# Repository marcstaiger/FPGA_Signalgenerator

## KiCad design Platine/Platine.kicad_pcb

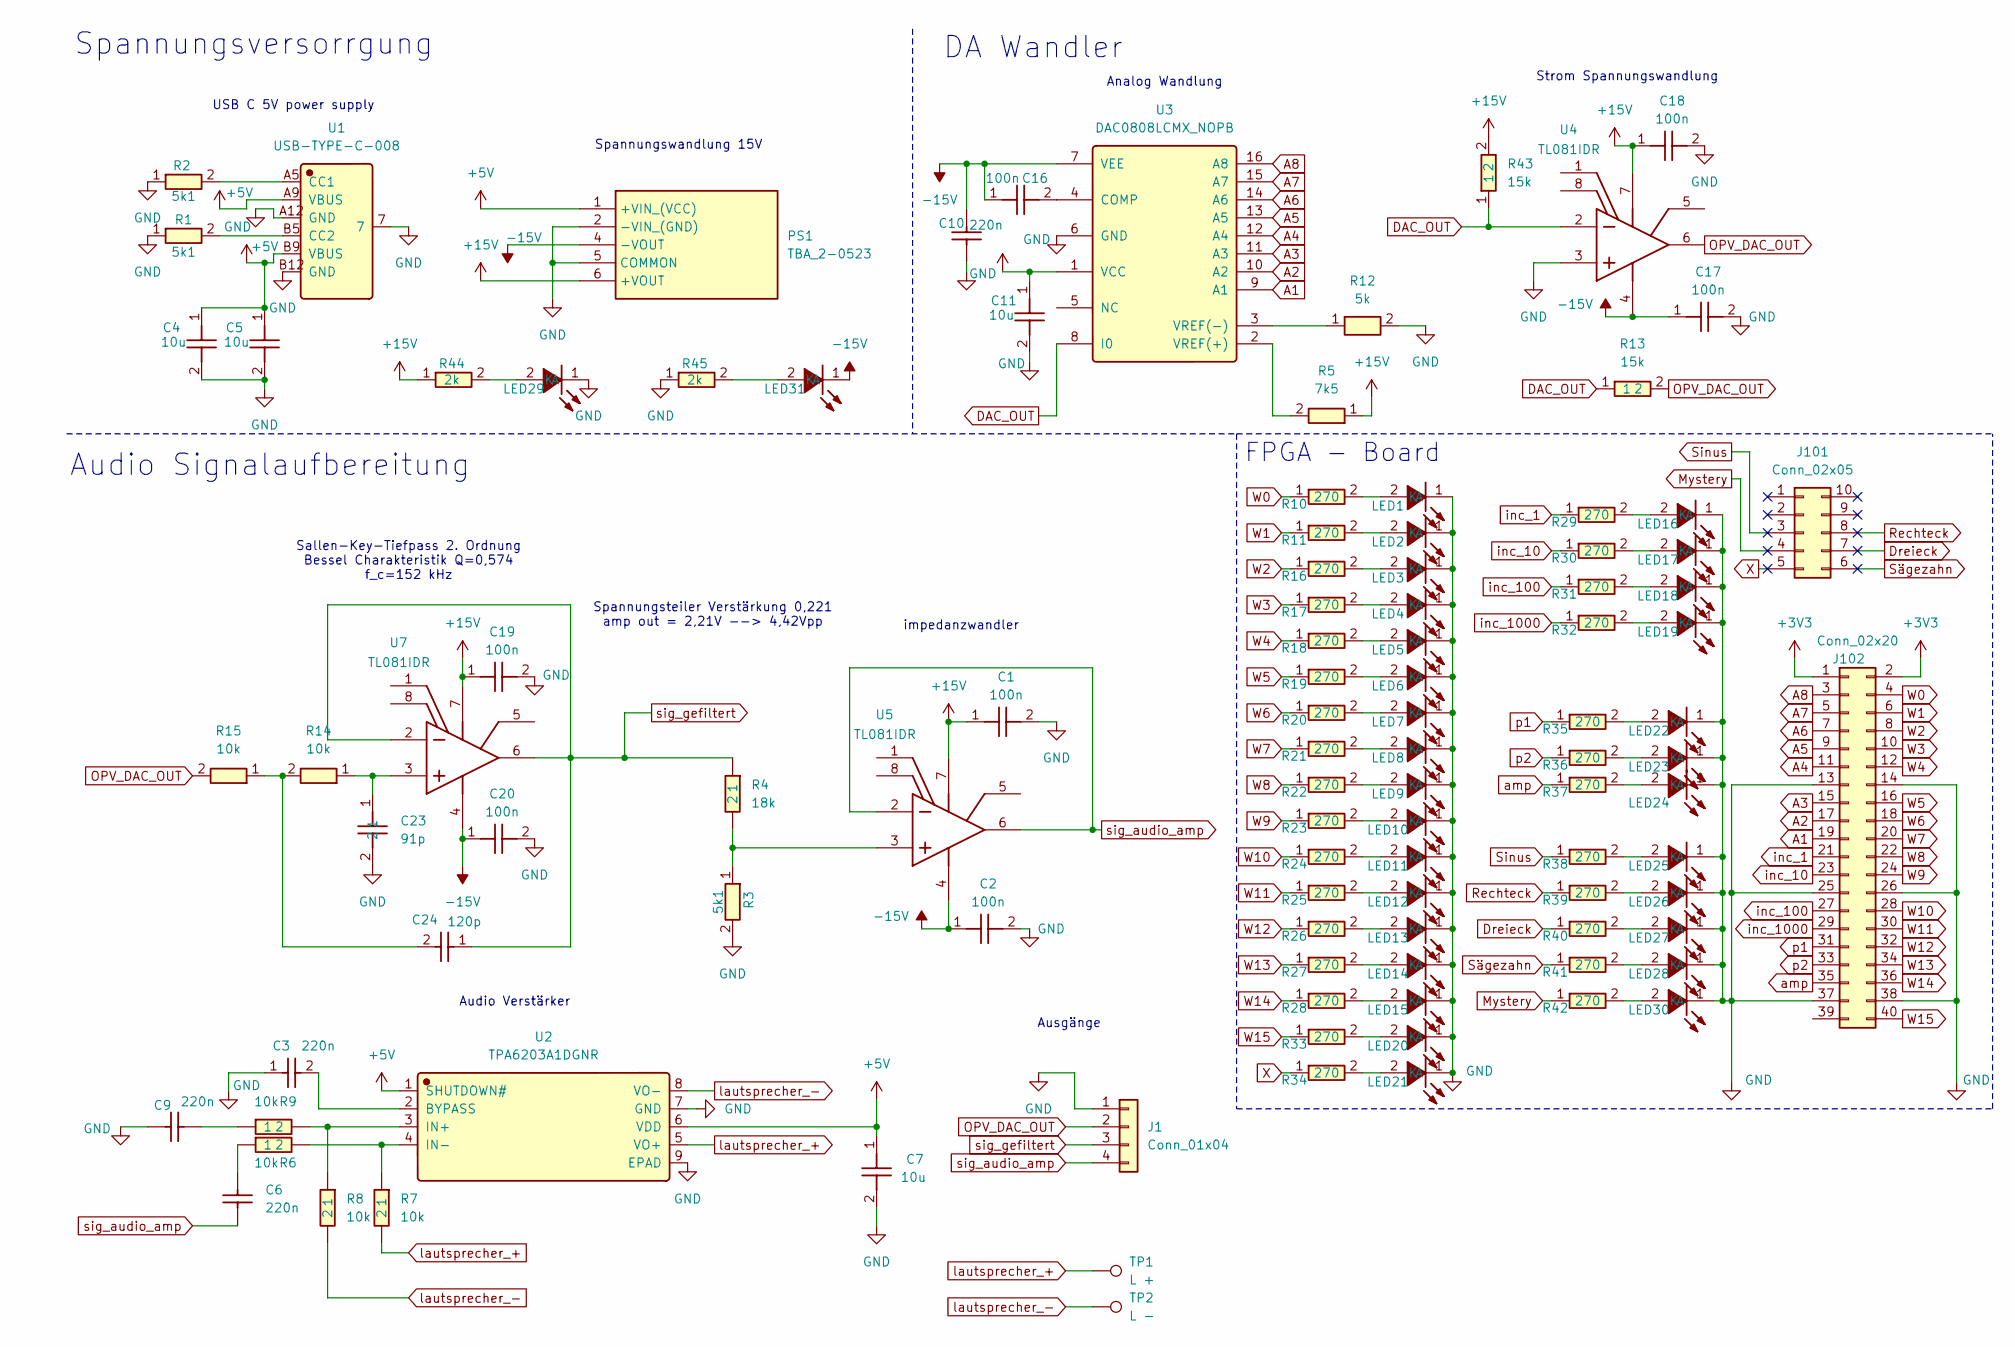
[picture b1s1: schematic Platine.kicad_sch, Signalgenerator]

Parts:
C1, C2, C16, C17, C18, C19, C20: 100n; CL05B104KO5NNNC; Manufacturer Part CL05B104KO5NNNC; LCSC C1525
C3, C6, C9, C10: 220n; CL21B224KBFNNNE; Manufacturer Part CL21B224KBFNNNE; LCSC C5378
C4, C5, C7, C11: 10u; CL21A106KAYNNNE; Manufacturer Part CL21A106KAYNNNE; LCSC C15850
C23: 91p; CC0402FRNPO9BN910; Manufacturer Part CC0402FRNPO9BN910; LCSC C541440
C24: 120p; GCM1555C1H121FA16D; Manufacturer Part GCM1555C1H121FA16D; LCSC C126496
J1: Conn_01x04; PinHeader_1x04_P2.54mm_Vertical
J101: Conn_02x05; PinHeader_2x05_P2.54mm_Vertical
J102: Conn_02x20; PinHeader_2x20_P2.54mm_Vertical
LED1: W0; KT-0603R; Manufacturer Part KT-0603R; LCSC C2286
LED2: W1; KT-0603R; Manufacturer Part KT-0603R; LCSC C2286
LED3: W2; KT-0603R; Manufacturer Part KT-0603R; LCSC C2286
LED4: W3; KT-0603R; Manufacturer Part KT-0603R; LCSC C2286
LED5: W4; KT-0603R; Manufacturer Part KT-0603R; LCSC C2286
LED6: W5; KT-0603R; Manufacturer Part KT-0603R; LCSC C2286
LED7: W6; KT-0603R; Manufacturer Part KT-0603R; LCSC C2286
LED8: W7; KT-0603R; Manufacturer Part KT-0603R; LCSC C2286
LED9: W8; KT-0603R; Manufacturer Part KT-0603R; LCSC C2286
LED10: W9; KT-0603R; Manufacturer Part KT-0603R; LCSC C2286
LED11: W10; KT-0603R; Manufacturer Part KT-0603R; LCSC C2286
LED12: W11; KT-0603R; Manufacturer Part KT-0603R; LCSC C2286
LED13: W12; KT-0603R; Manufacturer Part KT-0603R; LCSC C2286
LED14: W13; KT-0603R; Manufacturer Part KT-0603R; LCSC C2286
LED15: W14; KT-0603R; Manufacturer Part KT-0603R; LCSC C2286
LED16: inc_1; KT-0603R; Manufacturer Part KT-0603R; LCSC C2286
LED17: inc_10; KT-0603R; Manufacturer Part KT-0603R; LCSC C2286
LED18: inc_100; KT-0603R; Manufacturer Part KT-0603R; LCSC C2286
LED19: inc_1000; KT-0603R; Manufacturer Part KT-0603R; LCSC C2286
LED20: W15; KT-0603R; Manufacturer Part KT-0603R; LCSC C2286
LED21: X; KT-0603R; Manufacturer Part KT-0603R; LCSC C2286
LED22: p1; KT-0603R; Manufacturer Part KT-0603R; LCSC C2286
LED23: p2; KT-0603R; Manufacturer Part KT-0603R; LCSC C2286
LED24: amp; KT-0603R; Manufacturer Part KT-0603R; LCSC C2286
LED25: Sinus; KT-0603R; Manufacturer Part KT-0603R; LCSC C2286
LED26: Rechteck; KT-0603R; Manufacturer Part KT-0603R; LCSC C2286
LED27: Dreieck; KT-0603R; Manufacturer Part KT-0603R; LCSC C2286
LED28: Sägezahn; KT-0603R; Manufacturer Part KT-0603R; LCSC C2286
LED29: 15V; KT-0603R; Manufacturer Part KT-0603R; LCSC C2286
LED30: Mystery; KT-0603R; Manufacturer Part KT-0603R; LCSC C2286
LED31: -15V; KT-0603R; Manufacturer Part KT-0603R; LCSC C2286
PS1: TBA_2-0523; TBA20523; Manufacturer_Part_Number TBA 2-0523; LCSC C6547460
R1, R2, R3: 5k1; 0603WAF5101T5E; Manufacturer Part 0603WAF5101T5E; LCSC C23186
R4: 18k; 0603WAF1802T5E; Manufacturer Part 0603WAF1802T5E; LCSC C25810
R5: 7k5; 0603WAF7501T5E; Manufacturer Part 0603WAF7501T5E; LCSC C23234
R6, R7, R8, R9, R14, R15: 10k; 0603WAF1002T5E; Manufacturer Part 0603WAF1002T5E; LCSC C25804
R10: 270; RCT03270RJLF; Manufacturer Part RCT03270RJLF; LCSC C22966
R11, R16, R17, R18, R19, R20, R21, R22, R23, R24, R25, R26, R27, R28, R29, R30, R31, R32, R33, R34, R35, R36, R37, R38, R39, R40, R41, R42: 270; RCT03270RJLF; Manufacturer Part RCT03270RJLF; LCSC C177305
R12: 5k; P2TC0603D5001LNTA; Manufacturer Part P2TC0603D5001LNTA; LCSC C4095957
R13, R43: 15k; 0603WAF1502T5E; Manufacturer Part 0603WAF1502T5E; LCSC C22809
R44, R45: 2k; 0805W8F2001T5E; Manufacturer Part 0805W8F2001T5E; LCSC C17604
TP1: L +; Pin_D1.2mm_L11.3mm_W3.0mm_Flat
TP2: L -; Pin_D1.2mm_L11.3mm_W3.0mm_Flat
U1: USB-TYPE-C-008; Manufacturer Part USB-TYPE-C-008; LCSC C2927028
U2: TPA6203A1DGNR; Manufacturer Part TPA6203A1DGNR; LCSC C202146
U3: DAC0808LCMX_NOPB; Manufacturer Part DAC0808LCMX/NOPB; LCSC C132006
U4, U5, U7: TL081IDR; Manufacturer Part TL081IDR; LCSC C2057919

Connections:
+3V3: J102.1, J102.2
+5V: C4.1, C5.1, C7.1, C11.1, PS1.1 (+VIN_(VCC)), U1.A9 (VBUS), U1.B9 (VBUS), U2.1 (SHUTDOWN#), U2.6 (VDD), U3.1 (VCC)
+15V: C1.1, C18.1, C19.1, PS1.6 (+VOUT), R5.1, R43.2, R44.1, U4.7 (VCC+), U5.7 (VCC+), U7.7 (VCC+)
-15V: C2.1, C10.2, C16.1, C17.1, C20.1, LED31.1 (K), PS1.4 (-VOUT), U3.7 (VEE), U4.4 (VCC-), U5.4 (VCC-), U7.4 (VCC-)
A1: J102.19, U3.9 (A1)
A2: J102.17, U3.10 (A2)
A3: J102.15, U3.11 (A3)
A4: J102.11, U3.12 (A4)
A5: J102.9, U3.13 (A5)
A6: J102.7, U3.14 (A6)
A7: J102.5, U3.15 (A7)
A8: J102.3, U3.16 (A8)
DAC_OUT: R13.1, R43.1, U3.8 (I0), U4.2 (IN-)
Dreieck: J101.7, R40.1
GND: C1.2, C2.2, C3.1, C4.2, C5.2, C7.2, C9.2, C10.1, C11.2, C17.2, C18.2, C19.2, C20.2, C23.2, J1.1, J102.13, J102.14, J102.25, J102.26, J102.37, J102.38, LED1.1 (K), LED2.1 (K), LED3.1 (K), LED4.1 (K), LED5.1 (K), LED6.1 (K), LED7.1 (K), LED8.1 (K), LED9.1 (K), LED10.1 (K), LED11.1 (K), LED12.1 (K), LED13.1 (K), LED14.1 (K), LED15.1 (K), LED16.1 (K), LED17.1 (K), LED18.1 (K), LED19.1 (K), LED20.1 (K), LED21.1 (K), LED22.1 (K), LED23.1 (K), LED24.1 (K), LED25.1 (K), LED26.1 (K), LED27.1 (K), LED28.1 (K), LED29.1 (K), LED30.1 (K), PS1.2 (-VIN_(GND)), PS1.5 (COMMON), R1.1, R2.1, R3.2, R12.2, R45.1, U1.7, U1.A12 (GND), U1.B12 (GND), U2.7 (GND), U2.9 (EPAD), U3.6 (GND), U4.3 (IN+)
Mystery: J101.4, R42.1
unnamed: C6.2, R6.1
unnamed: C9.1, R9.1
unnamed: C24.2, R14.2, R15.1
unnamed: LED1.2 (A), R10.2
unnamed: LED2.2 (A), R11.2
unnamed: LED3.2 (A), R16.2
unnamed: LED4.2 (A), R17.2
unnamed: LED5.2 (A), R18.2
unnamed: LED6.2 (A), R19.2
unnamed: LED7.2 (A), R20.2
unnamed: LED8.2 (A), R21.2
unnamed: LED9.2 (A), R22.2
unnamed: LED10.2 (A), R23.2
unnamed: LED11.2 (A), R24.2
unnamed: LED12.2 (A), R25.2
unnamed: LED13.2 (A), R26.2
unnamed: LED14.2 (A), R27.2
unnamed: LED15.2 (A), R28.2
unnamed: LED16.2 (A), R29.2
unnamed: LED17.2 (A), R30.2
unnamed: LED18.2 (A), R31.2
unnamed: LED19.2 (A), R32.2
unnamed: LED20.2 (A), R33.2
unnamed: LED21.2 (A), R34.2
unnamed: LED22.2 (A), R35.2
unnamed: LED23.2 (A), R36.2
unnamed: LED24.2 (A), R37.2
unnamed: LED25.2 (A), R38.2
unnamed: LED26.2 (A), R39.2
unnamed: LED27.2 (A), R40.2
unnamed: LED28.2 (A), R41.2
unnamed: LED29.2 (A), R44.2
unnamed: LED30.2 (A), R42.2
unnamed: LED31.2 (A), R45.2
unnamed: R2.2, U1.A5 (CC1)
unnamed: R1.2, U1.B5 (CC2)
unnamed: C3.2, U2.2 (BYPASS)
unnamed: R8.1, R9.2, U2.3 (IN+)
unnamed: R6.2, R7.1, U2.4 (IN-)
unnamed: C16.2, U3.4 (COMP)
unnamed: R5.2, U3.2 (VREF(+))
unnamed: R12.1, U3.3 (VREF(-))
unnamed: R3.1, R4.2, U5.3 (IN+)
unnamed: C23.1, R14.1, U7.3 (IN+)
OPV_DAC_OUT: J1.2, R13.2, R15.2, U4.6 (OUT)
Rechteck: J101.8, R39.1
Sinus: J101.3, R38.1
Sägezahn: J101.6, R41.1
W0: J102.4, R10.1
W1: J102.6, R11.1
W2: J102.8, R16.1
W3: J102.10, R17.1
W4: J102.12, R18.1
W5: J102.16, R19.1
W6: J102.18, R20.1
W7: J102.20, R21.1
W8: J102.22, R22.1
W9: J102.24, R23.1
W10: J102.28, R24.1
W11: J102.30, R25.1
W12: J102.32, R26.1
W13: J102.34, R27.1
W14: J102.36, R28.1
W15: J102.40, R33.1
X: J101.5, R34.1
amp: J102.35, R37.1
inc_1: J102.21, R29.1
inc_10: J102.23, R30.1
inc_100: J102.27, R31.1
inc_1000: J102.29, R32.1
lautsprecher_+: R7.2, TP1.1, U2.5 (VO+)
lautsprecher_-: R8.2, TP2.1, U2.8 (VO-)
p1: J102.31, R35.1
p2: J102.33, R36.1
sig_audio_amp: C6.1, J1.4, U5.2 (IN-), U5.6 (OUT)
sig_gefiltert: C24.1, J1.3, R4.1, U7.2 (IN-), U7.6 (OUT)

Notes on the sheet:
Audio Signalaufbereitung
Audio Verstärker
Spannungsversorrgung
Ausgänge
Spannungsteiler Verstärkung 0,221 amp out = 2,21V --> 4,42Vpp
Spannungswandlung 15V
Analog Wandlung
FPGA - Board
Sallen-Key-Tiefpass 2. Ordnung Bessel Charakteristik Q=0,574 f_c=152 kHz
Strom Spannungswandlung
DA Wandler
USB C 5V power supply
impedanzwandler

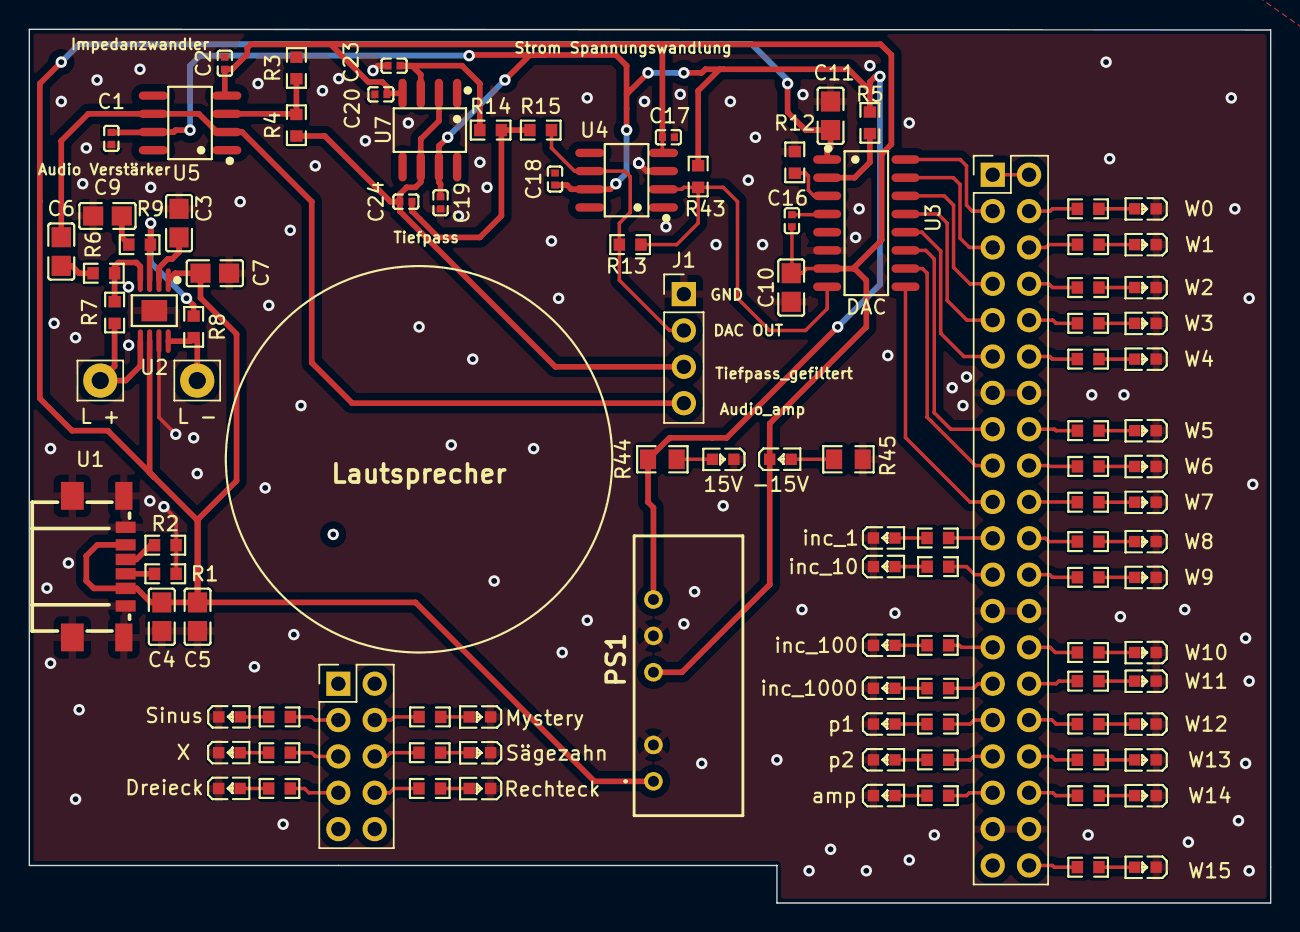
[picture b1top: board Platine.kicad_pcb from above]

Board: 2 copper layers, 86.7 x 61.0 mm, 106 parts (0 on the bottom side), 92 nets.

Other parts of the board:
Ge: LOGO; HFU-9mm

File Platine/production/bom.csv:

Designator,Footprint,Quantity,Value,LCSC Part #
"C1, C16, C17, C18, C19, C2, C20",CL05B104KO5NNNC,7,100n,C1525
"C10, C3, C6, C9",CL21B224KBFNNNE,4,220n,C5378
"C11, C4, C5, C7",CL21A106KAYNNNE,4,10u,C15850
C23,CC0402FRNPO9BN910,1,91p,C541440
C24,GCM1555C1H121FA16D,1,120p,C126496
J1,PinHeader_1x04_P2.54mm_Vertical,1,Conn_01x04,
J101,PinHeader_2x05_P2.54mm_Vertical,1,Conn_02x05,
J102,PinHeader_2x20_P2.54mm_Vertical,1,Conn_02x20,
LED1,KT-0603R,1,W0,C2286
LED10,KT-0603R,1,W9,C2286
LED11,KT-0603R,1,W10,C2286
LED12,KT-0603R,1,W11,C2286
LED13,KT-0603R,1,W12,C2286
LED14,KT-0603R,1,W13,C2286
LED15,KT-0603R,1,W14,C2286
LED16,KT-0603R,1,inc_1,C2286
LED17,KT-0603R,1,inc_10,C2286
LED18,KT-0603R,1,inc_100,C2286
LED19,KT-0603R,1,inc_1000,C2286
LED2,KT-0603R,1,W1,C2286
LED20,KT-0603R,1,W15,C2286
LED21,KT-0603R,1,X,C2286
LED22,KT-0603R,1,p1,C2286
LED23,KT-0603R,1,p2,C2286
LED24,KT-0603R,1,amp,C2286
LED25,KT-0603R,1,Sinus,C2286
LED26,KT-0603R,1,Rechteck,C2286
LED27,KT-0603R,1,Dreieck,C2286
LED28,KT-0603R,1,Sägezahn,C2286
LED29,KT-0603R,1,15V,C2286
LED3,KT-0603R,1,W2,C2286
LED30,KT-0603R,1,Mystery,C2286
LED31,KT-0603R,1,-15V,C2286
LED4,KT-0603R,1,W3,C2286
LED5,KT-0603R,1,W4,C2286
LED6,KT-0603R,1,W5,C2286
LED7,KT-0603R,1,W6,C2286
LED8,KT-0603R,1,W7,C2286
LED9,KT-0603R,1,W8,C2286
PS1,TBA20523,1,TBA_2-0523,C6547460
"R1, R2, R3",0603WAF5101T5E,3,5k1,C23186
"R10, R11, R16, R17, R18, R19, R20, R21, R22, R23, R24, R25, R26, R27, R28, R29, R30, R31, R32, R33, R34, R35, R36, R37, R38, R39, R40, R41, R42",RCT03270RJLF,29,270,C177305
R12,P2TC0603D5001LNTA,1,5k,C4095957
"R13, R43",0603WAF1502T5E,2,15k,C22809
"R14, R15, R6, R7, R8, R9",0603WAF1002T5E,6,10k,C25804
R4,0603WAF1802T5E,1,18k,C25810
"R44, R45",0805W8F2001T5E,2,2k,C17604
R5,0603WAF7501T5E,1,7k5,C23234
TP1,Pin_D1.2mm_L11.3mm_W3.0mm_Flat,1,L +,
TP2,Pin_D1.2mm_L11.3mm_W3.0mm_Flat,1,L -,
U1,USB-TYPE-C-008,1,USB-TYPE-C-008,C2927028
U2,TPA6203A1DGNR,1,TPA6203A1DGNR,C202146
U3,DAC0808LCMX_NOPB,1,DAC0808LCMX_NOPB,C132006
"U4, U5, U7",TL081IDR,3,TL081IDR,C2057919
